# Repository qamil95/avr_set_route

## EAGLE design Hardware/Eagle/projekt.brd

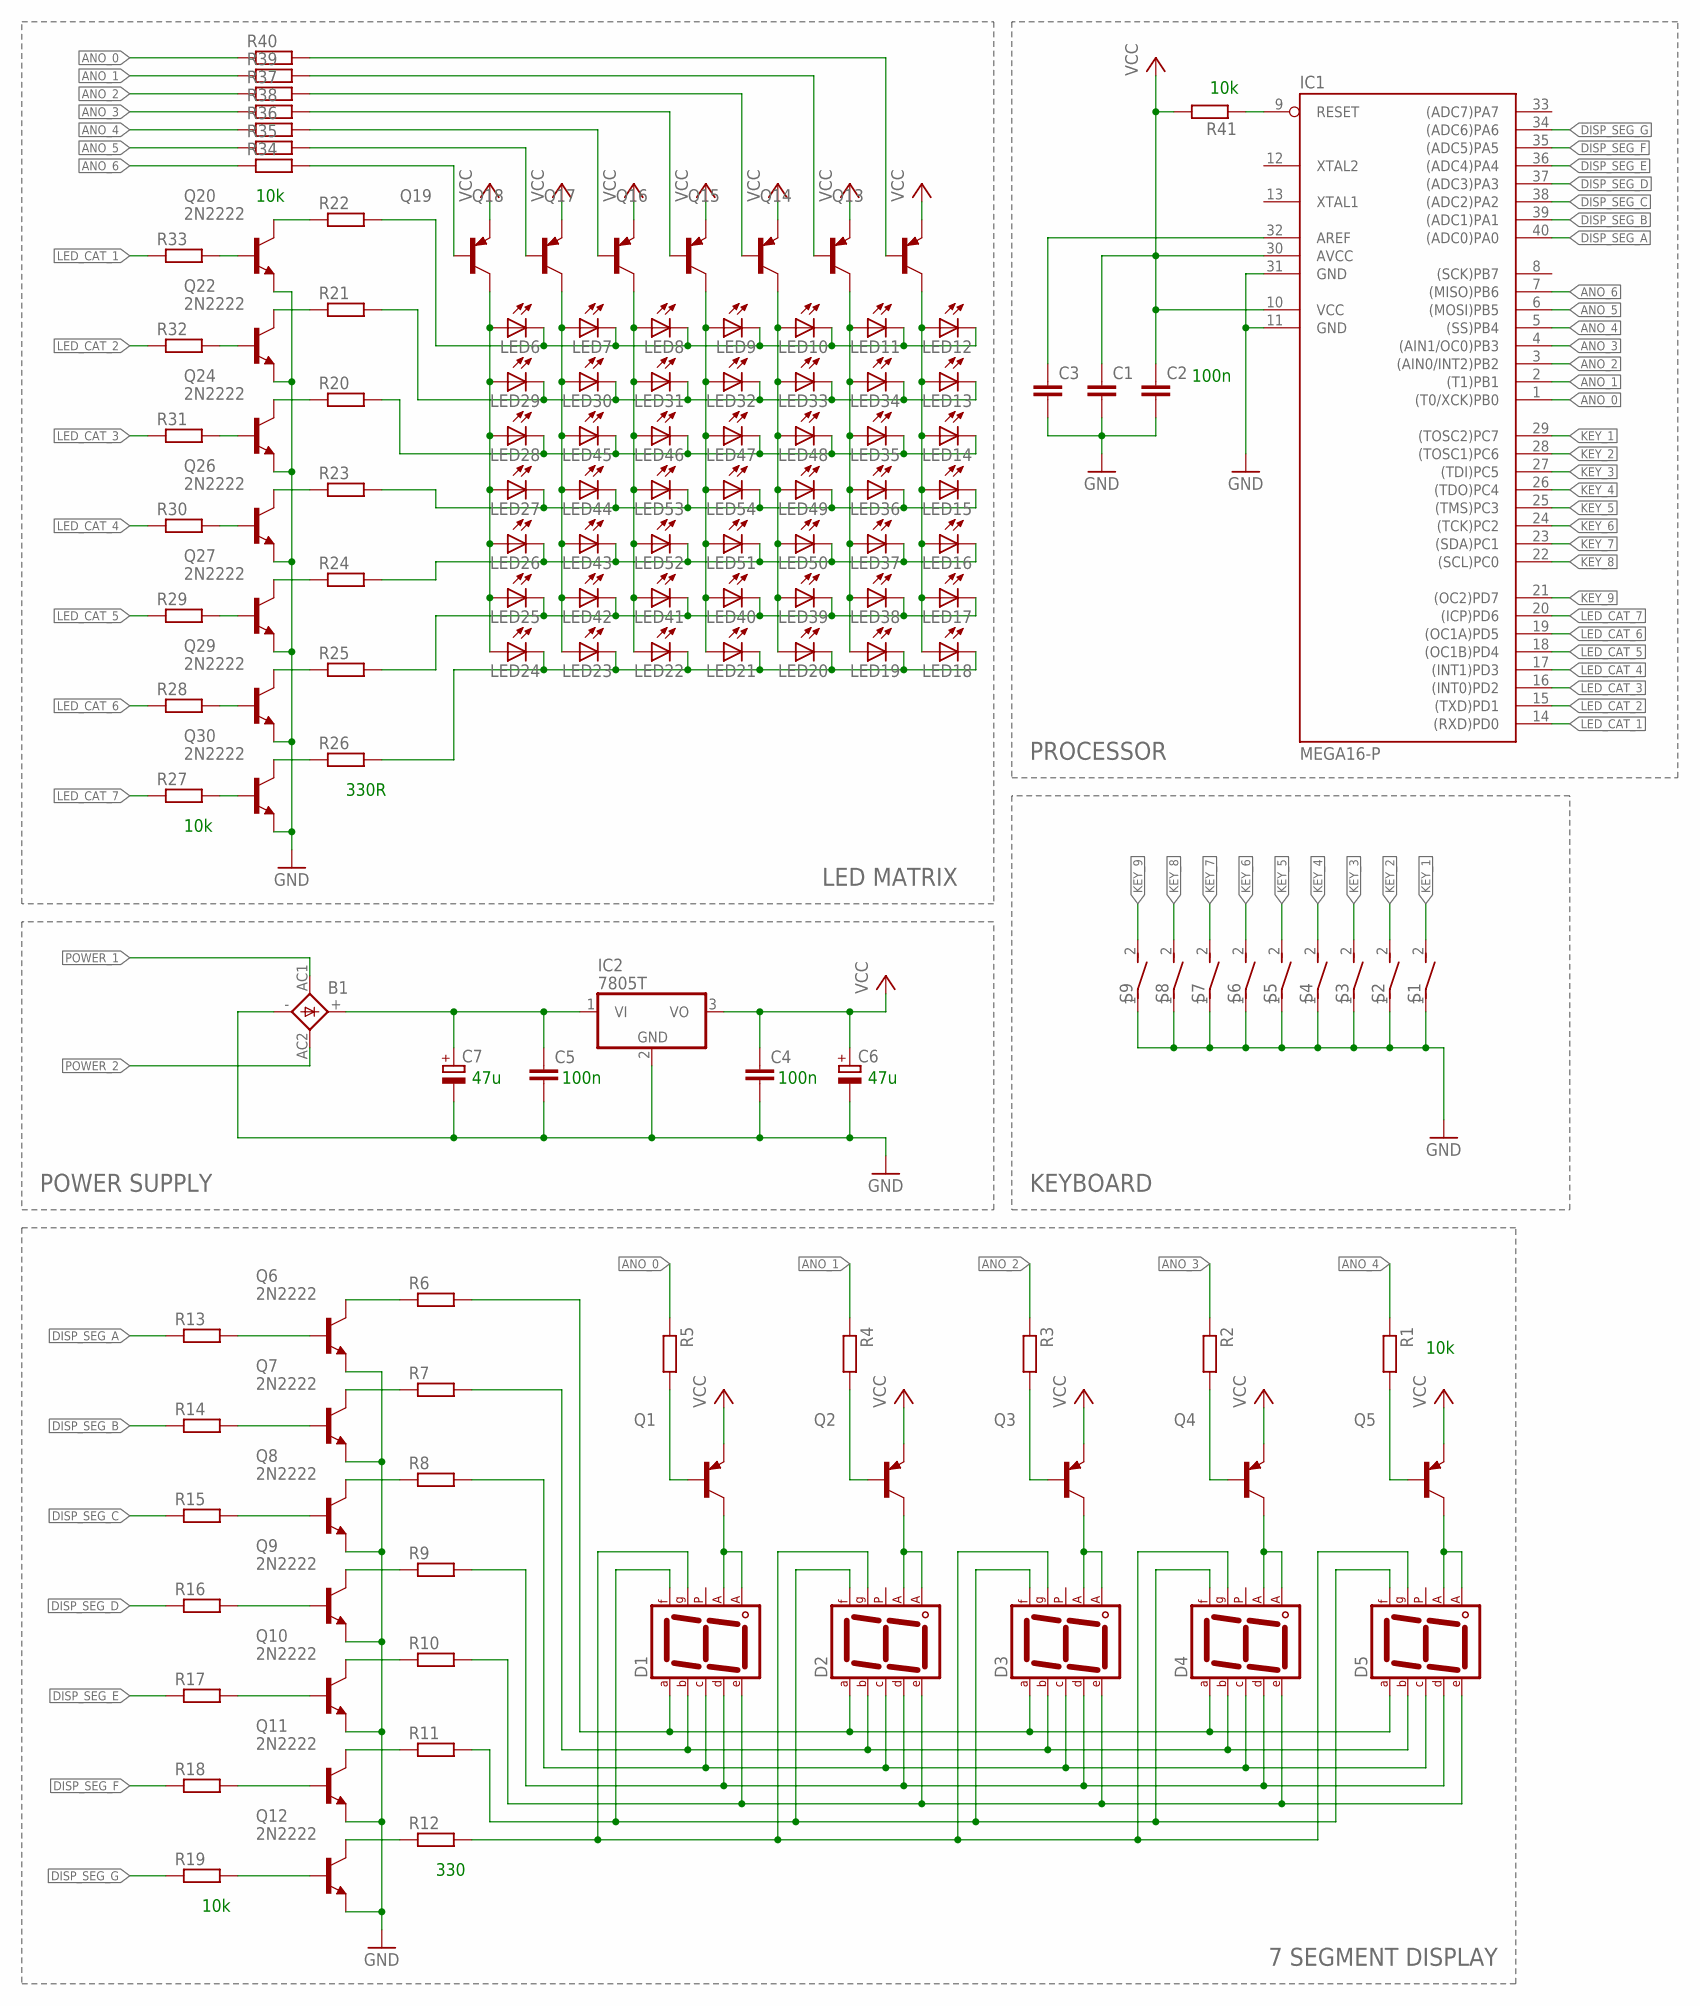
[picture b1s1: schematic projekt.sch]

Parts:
B1: KBU
C1, C2, C3, C4, C5: C5/7.2; C5B7.2
C6, C7: CPOL-EUB45181C; B45181C
D1, D2, D3, D4, D5: 7SEG-CA; 7SEG-13
IC1: MEGA16-P; DIL40
IC2: 7805T; TO220H
LED6, LED7, LED8, LED9, LED10, LED11, LED12, LED13, LED14, LED15, LED16, LED17, LED18, LED19, LED20, LED21, LED22, LED23, LED24, LED25, LED26, LED27, LED28, LED29, LED30, LED31, LED32, LED33, LED34, LED35, LED36, LED37, LED38, LED39, LED40, LED41, LED42, LED43, LED44, LED45, LED46, LED47, LED48, LED49, LED50, LED51, LED52, LED53, LED54: LED3MM
Q1, Q2, Q3, Q4, Q5, Q13, Q14, Q15, Q16, Q17, Q18, Q19: -PNP-TO18-; TO18-
Q6, Q7, Q8, Q9, Q10, Q11, Q12, Q20, Q22, Q24, Q26, Q27, Q29, Q30: 2N2222; TO18
R1, R2, R3, R4, R5, R6, R7, R8, R9, R10, R11, R12, R13, R14, R15, R16, R17, R18, R19, R20, R21, R22, R23, R24, R25, R26, R27, R28, R29, R30, R31, R32, R33, R34, R35, R36, R37, R38, R39, R40, R41: R-EU_0204/5; 0204/5
S1, S2, S3, S4, S5, S6, S7, S8, S9: DS01E; DS-01

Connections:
ANO_0: IC1.1 ((T0/XCK)PB0), R5.1, R40.1
ANO_1: IC1.2 ((T1)PB1), R4.1, R39.1
ANO_2: IC1.3 ((AIN0/INT2)PB2), R3.1, R37.1
ANO_3: IC1.4 ((AIN1/OC0)PB3), R2.1, R38.1
ANO_4: IC1.5 ((SS)PB4), R1.1, R36.1
ANO_5: IC1.6 ((MOSI)PB5), R35.1
ANO_6: IC1.7 ((MISO)PB6), R34.1
DISP_SEG_A: IC1.40 ((ADC0)PA0), R13.1
DISP_SEG_B: IC1.39 ((ADC1)PA1), R14.1
DISP_SEG_C: IC1.38 ((ADC2)PA2), R15.1
DISP_SEG_D: IC1.37 ((ADC3)PA3), R16.1
DISP_SEG_E: IC1.36 ((ADC4)PA4), R17.1
DISP_SEG_F: IC1.35 ((ADC5)PA5), R18.1
DISP_SEG_G: IC1.34 ((ADC6)PA6), R19.1
GND: B1.-, C1.2, C2.2, C3.2, C4.2, C5.2, C6.-, C7.-, IC1.11 (GND), IC1.31 (GND), IC2.2 (GND), Q6.1 (E), Q7.1 (E), Q8.1 (E), Q9.1 (E), Q10.1 (E), Q11.1 (E), Q12.1 (E), Q20.1 (E), Q22.1 (E), Q24.1 (E), Q26.1 (E), Q27.1 (E), Q29.1 (E), Q30.1 (E), S1.1, S2.1, S3.1, S4.1, S5.1, S6.1, S7.1, S8.1, S9.1
KEY_1: IC1.29 ((TOSC2)PC7), S1.2
KEY_2: IC1.28 ((TOSC1)PC6), S2.2
KEY_3: IC1.27 ((TDI)PC5), S3.2
KEY_4: IC1.26 ((TDO)PC4), S4.2
KEY_5: IC1.25 ((TMS)PC3), S5.2
KEY_6: IC1.24 ((TCK)PC2), S6.2
KEY_7: IC1.23 ((SDA)PC1), S7.2
KEY_8: IC1.22 ((SCL)PC0), S8.2
KEY_9: IC1.21 ((OC2)PD7), S9.2
LED_CAT_1: IC1.14 ((RXD)PD0), R33.1
LED_CAT_2: IC1.15 ((TXD)PD1), R32.1
LED_CAT_3: IC1.16 ((INT0)PD2), R31.1
LED_CAT_4: IC1.17 ((INT1)PD3), R30.1
LED_CAT_5: IC1.18 ((OC1B)PD4), R29.1
LED_CAT_6: IC1.19 ((OC1A)PD5), R28.1
LED_CAT_7: IC1.20 ((ICP)PD6), R27.1
unnamed: D1.7 (A), D2.7 (A), D3.7 (A), D4.7 (A), D5.7 (A), R6.2
unnamed: D1.6 (B), D2.6 (B), D3.6 (B), D4.6 (B), D5.6 (B), R7.2
unnamed: D1.4 (C), D2.4 (C), D3.4 (C), D4.4 (C), D5.4 (C), R8.2
unnamed: D1.2 (D), D2.2 (D), D3.2 (D), D4.2 (D), D5.2 (D), R9.2
unnamed: D1.1 (E), D2.1 (E), D3.1 (E), D4.1 (E), D5.1 (E), R10.2
unnamed: D1.9 (F), D2.9 (F), D3.9 (F), D4.9 (F), D5.9 (F), R11.2
unnamed: D1.3 (CA1), D1.8 (CA2), Q1.3 (C)
unnamed: D2.3 (CA1), D2.8 (CA2), Q2.3 (C)
unnamed: D3.3 (CA1), D3.8 (CA2), Q3.3 (C)
unnamed: D4.3 (CA1), D4.8 (CA2), Q4.3 (C)
unnamed: D5.3 (CA1), D5.8 (CA2), Q5.3 (C)
unnamed: Q1.2 (B), R5.2
unnamed: Q2.2 (B), R4.2
unnamed: Q3.2 (B), R3.2
unnamed: Q4.2 (B), R2.2
unnamed: Q5.2 (B), R1.2
unnamed: Q6.3 (C), R6.1
unnamed: Q7.3 (C), R7.1
unnamed: Q8.3 (C), R8.1
unnamed: Q9.3 (C), R9.1
unnamed: Q10.3 (C), R10.1
unnamed: Q11.3 (C), R11.1
unnamed: Q12.3 (C), R12.1
unnamed: D1.10 (G), D2.10 (G), D3.10 (G), D4.10 (G), D5.10 (G), R12.2
unnamed: B1.+, C5.1, C7.+, IC2.1 (VI)
unnamed: Q8.2 (B), R15.2
unnamed: Q9.2 (B), R16.2
unnamed: Q10.2 (B), R17.2
unnamed: Q11.2 (B), R18.2
unnamed: Q7.2 (B), R14.2
unnamed: Q6.2 (B), R13.2
unnamed: Q12.2 (B), R19.2
unnamed: LED13.K (C), LED29.K (C), LED30.K (C), LED31.K (C), LED32.K (C), LED33.K (C), LED34.K (C), R21.2
unnamed: LED14.K (C), LED28.K (C), LED35.K (C), LED45.K (C), LED46.K (C), LED47.K (C), LED48.K (C), R20.2
unnamed: LED15.K (C), LED27.K (C), LED36.K (C), LED44.K (C), LED49.K (C), LED53.K (C), LED54.K (C), R23.2
unnamed: LED16.K (C), LED26.K (C), LED37.K (C), LED43.K (C), LED50.K (C), LED51.K (C), LED52.K (C), R24.2
unnamed: LED17.K (C), LED25.K (C), LED38.K (C), LED39.K (C), LED40.K (C), LED41.K (C), LED42.K (C), R25.2
unnamed: LED18.K (C), LED19.K (C), LED20.K (C), LED21.K (C), LED22.K (C), LED23.K (C), LED24.K (C), R26.2
unnamed: LED6.A, LED24.A, LED25.A, LED26.A, LED27.A, LED28.A, LED29.A, Q19.3 (C)
unnamed: LED7.A, LED23.A, LED30.A, LED42.A, LED43.A, LED44.A, LED45.A, Q18.3 (C)
unnamed: LED8.A, LED22.A, LED31.A, LED41.A, LED46.A, LED52.A, LED53.A, Q17.3 (C)
unnamed: LED9.A, LED21.A, LED32.A, LED40.A, LED47.A, LED51.A, LED54.A, Q16.3 (C)
unnamed: LED10.A, LED20.A, LED33.A, LED39.A, LED48.A, LED49.A, LED50.A, Q15.3 (C)
unnamed: LED11.A, LED19.A, LED34.A, LED35.A, LED36.A, LED37.A, LED38.A, Q14.3 (C)
unnamed: LED12.A, LED13.A, LED14.A, LED15.A, LED16.A, LED17.A, LED18.A, Q13.3 (C)
unnamed: Q30.3 (C), R26.1
unnamed: LED6.K (C), LED7.K (C), LED8.K (C), LED9.K (C), LED10.K (C), LED11.K (C), LED12.K (C), R22.2
unnamed: Q13.2 (B), R40.2
unnamed: Q29.3 (C), R25.1
unnamed: Q27.3 (C), R24.1
unnamed: Q26.3 (C), R23.1
unnamed: Q24.3 (C), R20.1
unnamed: Q22.3 (C), R21.1
unnamed: Q20.3 (C), R22.1
unnamed: Q20.2 (B), R33.2
unnamed: Q22.2 (B), R32.2
unnamed: Q26.2 (B), R30.2
unnamed: Q24.2 (B), R31.2
unnamed: Q27.2 (B), R29.2
unnamed: Q29.2 (B), R28.2
unnamed: Q30.2 (B), R27.2
unnamed: Q18.2 (B), R35.2
unnamed: Q17.2 (B), R36.2
unnamed: Q15.2 (B), R37.2
unnamed: Q19.2 (B), R34.2
unnamed: Q16.2 (B), R38.2
unnamed: Q14.2 (B), R39.2
unnamed: IC1.9 (RESET), R41.1
unnamed: C3.1, IC1.32 (AREF)
POWER_1: B1.AC1
POWER_2: B1.AC2
VCC: C1.1, C2.1, C4.1, C6.+, IC1.10 (VCC), IC1.30 (AVCC), IC2.3 (VO), Q1.1 (E), Q2.1 (E), Q3.1 (E), Q4.1 (E), Q5.1 (E), Q13.1 (E), Q14.1 (E), Q15.1 (E), Q16.1 (E), Q17.1 (E), Q18.1 (E), Q19.1 (E), R41.2

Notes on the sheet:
10k
330
330R
100n
KEYBOARD
POWER SUPPLY
47u
7 SEGMENT DISPLAY
PROCESSOR
LED MATRIX

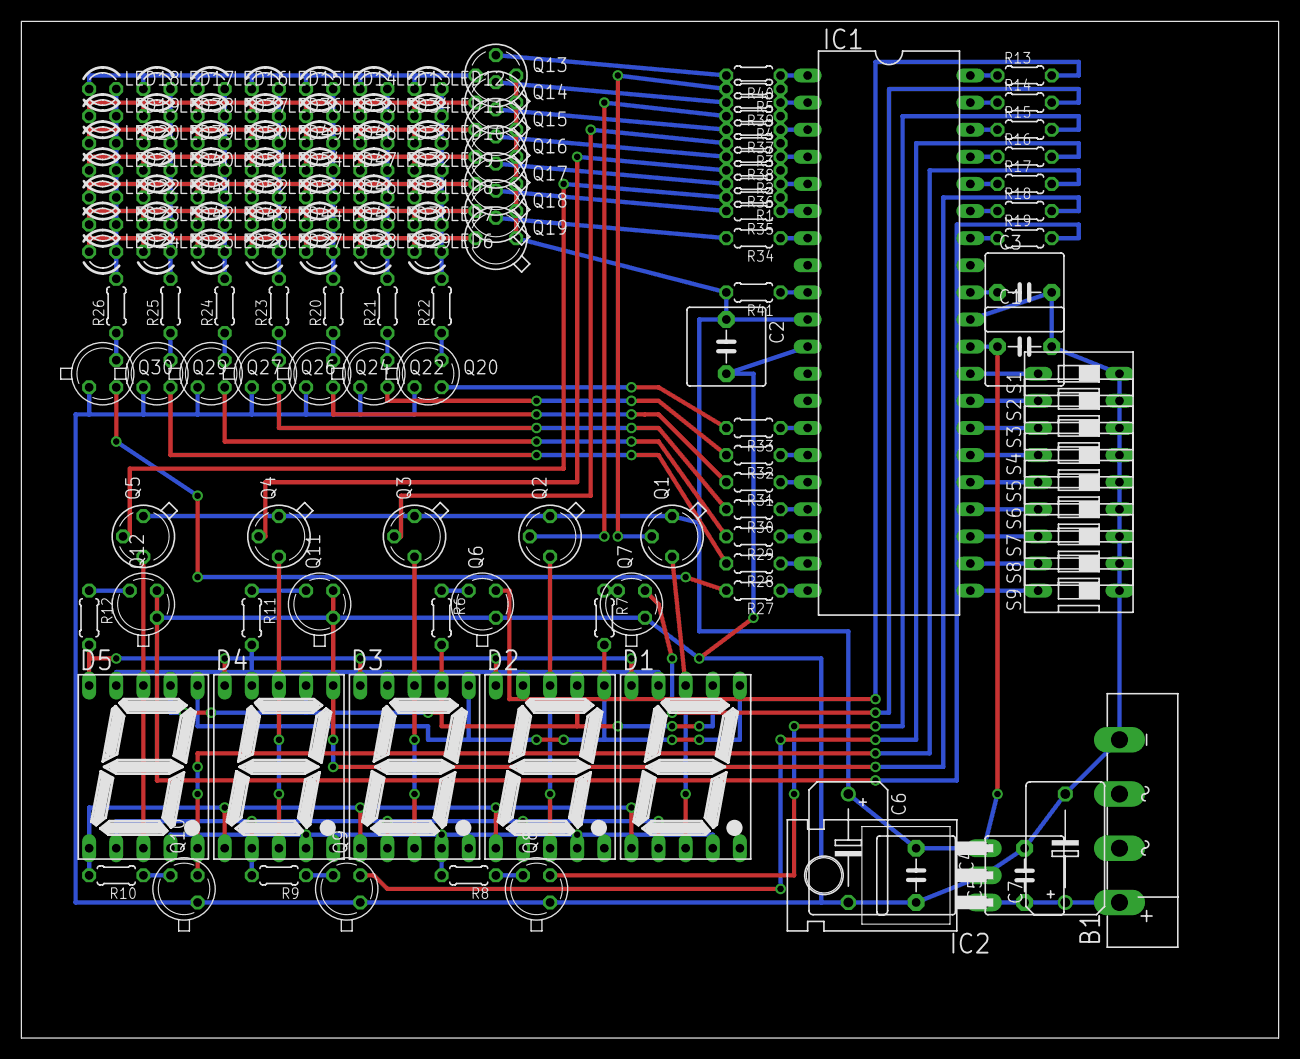
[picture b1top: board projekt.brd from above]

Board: 2 copper layers, 117.8 x 95.2 mm, 140 parts (0 on the bottom side), 101 nets.

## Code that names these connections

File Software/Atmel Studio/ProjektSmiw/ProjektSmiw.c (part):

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
#define delay_time 400 //odwie¿anie wywietlaczy i diod

#define blue_button (!(PINC & (1<<PC5))) //niebieski przycisk na panelu, true jeli wciniêty
#define debugmode (!(PINB & (1<<PB7))) //tryb testowy, true jeli SCK zwarte do masy
#define switch_up (PINA & (1<<PA7)) //prze³¹cznik na panelu, true jeli w górze

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/************************************************************************/
void refresh_switches()
{
	if (PINC & (1<<PC6))	switches |= (1<<0); else switches &= ~(1<<0);		
	if (!(PINC & (1<<PC7)))	switches |= (1<<1); else switches &= ~(1<<1);	
	if (PINC & (1<<PC1))	switches |= (1<<2); else switches &= ~(1<<2);		
	if (!(PINC & (1<<PC3)))	switches |= (1<<3); else switches &= ~(1<<3);		
	if (!(PINC & (1<<PC2)))	switches |= (1<<4); else switches &= ~(1<<4);	
	if (PINC & (1<<PC4))	switches |= (1<<5); else switches &= ~(1<<5);	
	if (PIND & (1<<PD7))	switches |= (1<<6); else switches &= ~(1<<6);	
	if (!(PINC & (1<<PC0)))	switches |= (1<<7); else switches &= ~(1<<7);
}

/************************************************************************/
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
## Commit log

2016-11-14 add README
2016-11-14 Testowy commit
2016-11-16 aktualizacja schematu
2016-11-17 pierwsza wersja zasilania
2016-11-23 aktualizacja danych katalogowych - kupione czesci
2016-11-23 test wyswietlacza 7segmentowego
2016-11-25 generalne porzadki w kodzie i schemacie
2016-11-30 diody i klawiatura
2016-12-06 multiplekser zamiast klawiatury matrycowej
2016-12-08 przerwania, multiplekser
2016-12-10 wymiana klawiatury
2016-12-11 prezentacja
2017-02-03 gaszeniei zapalanie ledow
2017-02-04 debugmode
2017-02-05 pierwsza wersja gry
2017-02-07 aktualizacja raportu koncowego
2017-02-08 opis trybu testowego
